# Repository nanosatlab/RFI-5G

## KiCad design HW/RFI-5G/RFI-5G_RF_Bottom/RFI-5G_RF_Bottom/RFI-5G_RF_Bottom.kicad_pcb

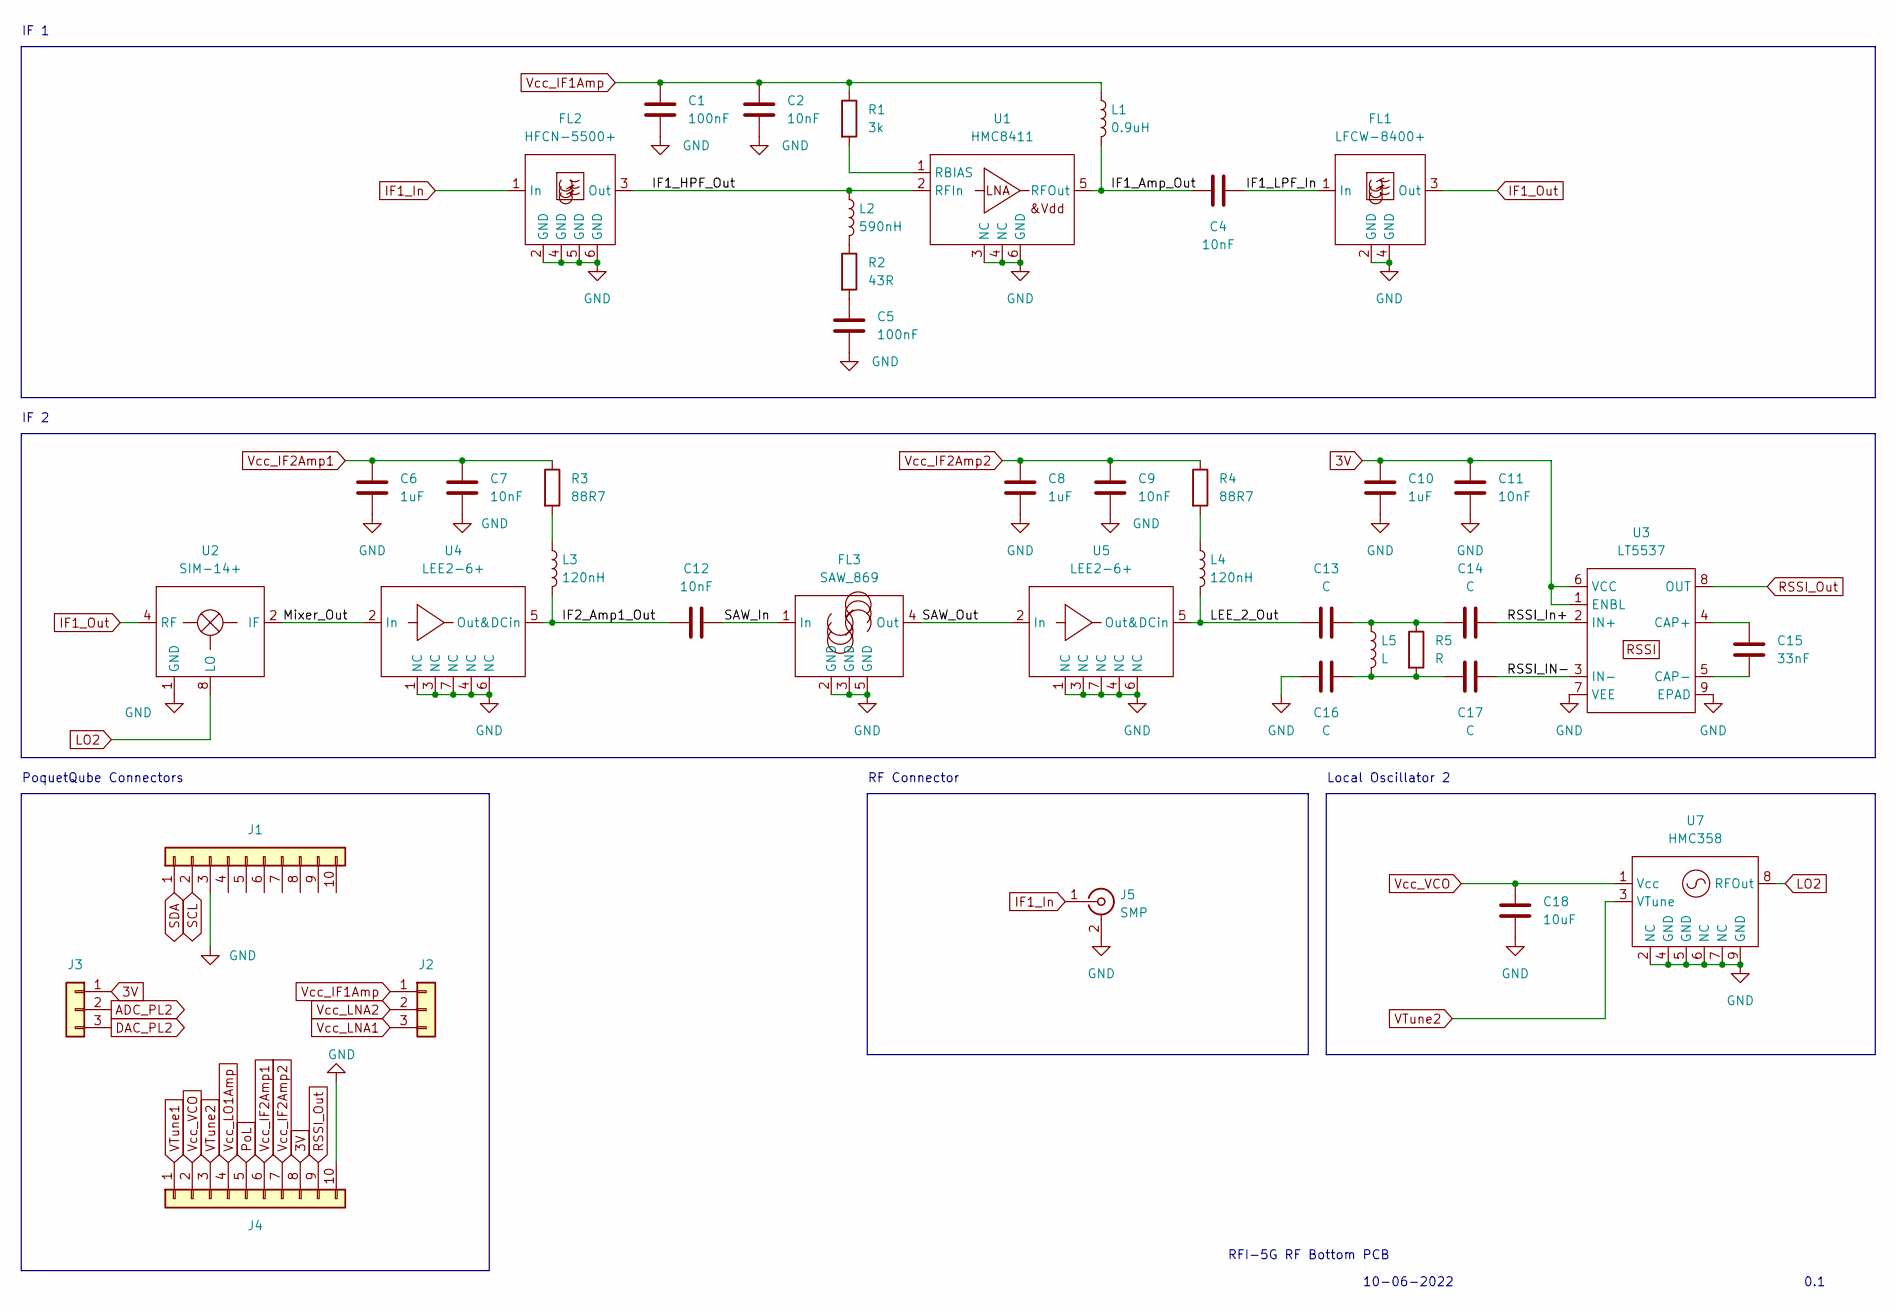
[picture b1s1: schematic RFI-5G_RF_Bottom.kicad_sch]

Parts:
C1, C5: 100nF; C_0402_1005Metric
C2, C4, C7, C9, C11, C12: 10nF; C_0402_1005Metric
C6, C8, C10: 1uF; C_0402_1005Metric
C13, C14, C16, C17: C; C_0402_1005Metric
C15: 33nF; C_0402_1005Metric
C18: 10uF; C_0402_1005Metric
FL1: LFCW-8400+; JC0603C-1
FL2: HFCN-5500+; JC0603C
FL3: SAW_869; QCS5P
J1, J4: Conn_01x10; PinHeader_1x10_P2.54mm_Vertical
J2, J3: Conn_01x03; PinHeader_1x03_P2.54mm_Vertical
J5: SMP; SMP_StraightPlugPCB
L1: 0.9uH; L_0603_1608Metric
L2: 590nH; L_0603_1608Metric
L3, L4: 120nH; L_0603_1608Metric
L5: L; L_0603_1608Metric
R1: 3k; R_0603_1608Metric
R2: 43R; R_0603_1608Metric
R3, R4: 88R7; R_0603_1608Metric
R5: R; R_0603_1608Metric
U1: HMC8411; 6-LFCSP
U2: SIM-14+; HV1195
U3: LT5537; DFN-8-1EP_2x3mm_P0.5mm_EP0.56x2.15mm
U4, U5: LEE2-6+; WSON-6-1EP_2x2mm_P0.65mm_EP1x1.6mm
U7: HMC358; MSOP-8-1EP_3x3mm_P0.65mm_EP2.5x3mm_Mask1.73x2.36mm

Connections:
3V: C10.2, C11.2, J3.1, J4.8, U3.1 (ENBL), U3.6 (VCC)
/IF1_Amp_Out: C4.1, L1.2, U1.5 (RFOut)
/IF1_HPF_Out: FL2.3 (Out), L2.1, U1.2 (RFIn)
/IF1_LPF_In: C4.2, FL1.1 (In)
/IF2_Amp1_Out: C12.1, L3.2, U4.5 (Out&DCin)
/LEE_2_Out: C13.1, L4.2, U5.5 (Out&DCin)
/Mixer_Out: U2.2 (IF), U4.2 (In)
/RSSI_IN-: C17.2, U3.3 (IN-)
/RSSI_In+: C14.2, U3.2 (IN+)
/SAW_In: C12.2, FL3.1 (In)
/SAW_Out: FL3.4 (Out), U5.2 (In)
ADC_PL2: J3.2
DAC_PL2: J3.3
GND: C1.1, C2.1, C5.1, C6.1, C7.1, C8.1, C9.1, C10.1, C11.1, C16.1, C18.1, FL1.2 (GND), FL1.4 (GND), FL2.2 (GND), FL2.4 (GND), FL2.5 (GND), FL2.6 (GND), FL3.2 (GND), FL3.3 (GND), FL3.5 (GND), J1.3, J4.10, J5.2 (Ext), U1.3 (NC), U1.4 (NC), U1.6 (GND), U2.1 (GND), U3.7 (VEE), U3.9 (EPAD), U4.1 (NC), U4.3 (NC), U4.4 (NC), U4.6 (NC), U4.7 (NC), U5.1 (NC), U5.3 (NC), U5.4 (NC), U5.6 (NC), U5.7 (NC), U7.2 (NC), U7.4 (GND), U7.5 (GND), U7.6 (NC), U7.7 (NC), U7.9 (GND)
IF1_In: FL2.1 (In), J5.1 (In)
IF1_Out: FL1.3 (Out), U2.4 (RF)
LO2: U2.8 (LO), U7.8 (RFOut)
unnamed: C5.2, R2.2
unnamed: C13.2, C14.1, L5.1, R5.1
unnamed: C15.1, U3.4 (CAP+)
unnamed: C15.2, U3.5 (CAP-)
unnamed: C16.2, C17.1, L5.2, R5.2
unnamed: L2.2, R2.1
unnamed: L3.1, R3.2
unnamed: L4.1, R4.2
unnamed: R1.2, U1.1 (RBIAS)
PoL: J4.5
RSSI_Out: J4.9, U3.8 (OUT)
SCL: J1.2
SDA: J1.1
VTune1: J4.1
VTune2: J4.3, U7.3 (VTune)
Vcc_IF1Amp: C1.2, C2.2, J2.1, L1.1, R1.1
Vcc_IF2Amp1: C6.2, C7.2, J4.6, R3.1
Vcc_IF2Amp2: C8.2, C9.2, J4.7, R4.1
Vcc_LNA1: J2.3
Vcc_LNA2: J2.2
Vcc_LO1Amp: J4.4
Vcc_VCO: C18.2, J4.2, U7.1 (Vcc)

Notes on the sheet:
Local Oscillator 2
0.1
IF 2
IF 1
RFI-5G RF Bottom PCB
RF Connector
10-06-2022
PoquetQube Connectors

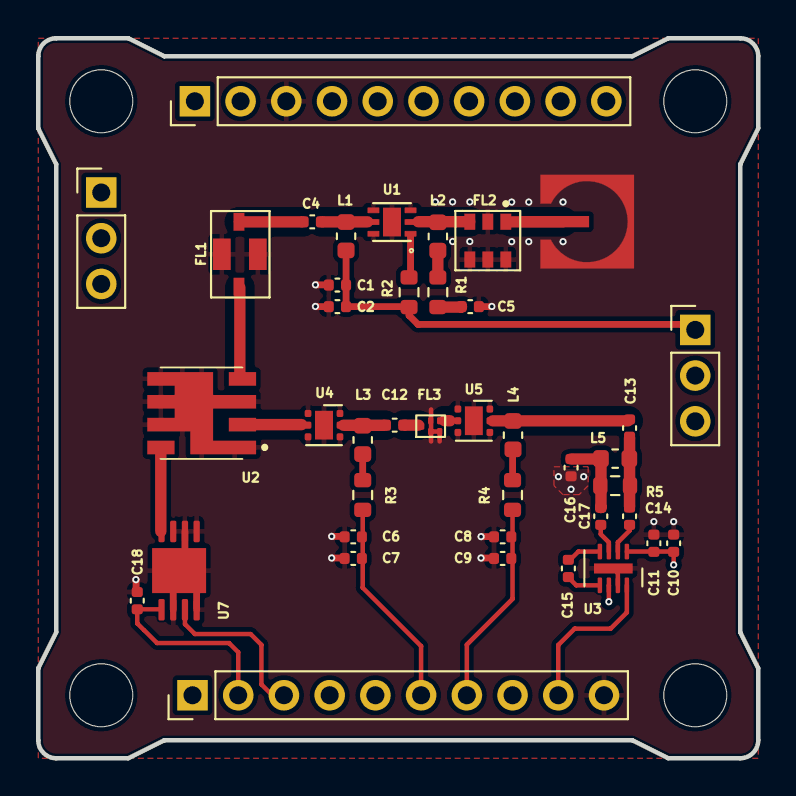
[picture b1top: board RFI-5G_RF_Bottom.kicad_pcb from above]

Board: 2 copper layers, 40.0 x 40.0 mm, 41 parts (0 on the bottom side), 30 nets.

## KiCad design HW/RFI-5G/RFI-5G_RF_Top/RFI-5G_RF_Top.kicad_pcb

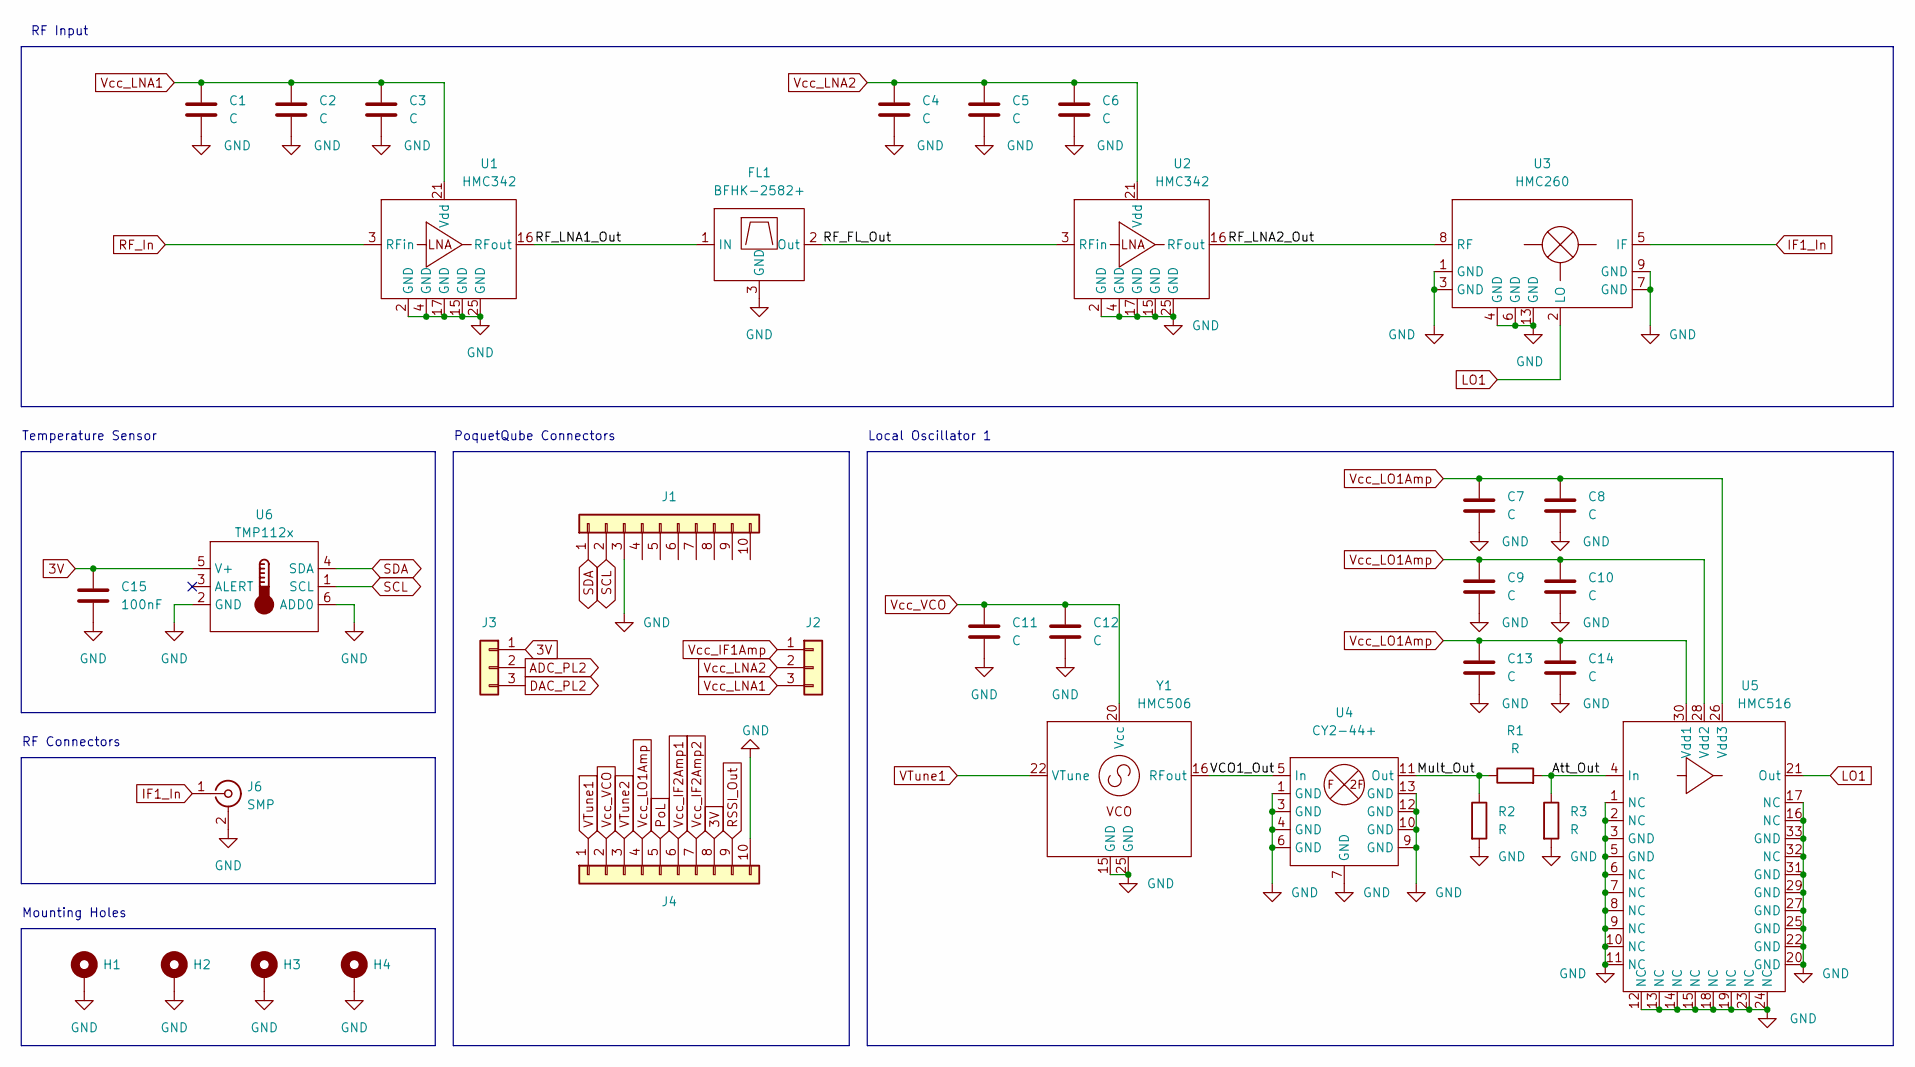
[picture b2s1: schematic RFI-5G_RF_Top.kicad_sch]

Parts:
C1, C2, C3, C4, C5, C6, C7, C8, C9, C10, C11, C12, C13, C14: C; C_0402_1005Metric
C15: 100nF; C_0402_1005Metric
FL1: BFHK-2582+; NM1812C-2
H1, H2, H3, H4: MountingHole_Pad
J1, J4: Conn_01x10; PinHeader_1x10_P2.54mm_Vertical
J2, J3: Conn_01x03; PinHeader_1x03_P2.54mm_Vertical
J6: SMP; SMP_StraightPlugPCB
R1, R2, R3: R; R_0402_1005Metric
U1, U2: HMC342; QFN-24-1EP_4x4mm_P0.5mm_EP2.6x2.6mm
U3: HMC260; QFN-12-1EP_3x3mm_P0.5mm_EP1.6x1.6mm
U4: CY2-44+; QFN-12-1EP_3x3mm_P0.5mm_EP1.65x1.65mm
U5: HMC516; QFN-32-1EP_5x5mm_P0.5mm_EP3.6x3.6mm
U6: TMP112x; SOT-563
Y1: HMC506; QFN-24-1EP_4x4mm_P0.5mm_EP2.7x2.7mm

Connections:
3V: C15.2, J3.1, J4.8, U6.5 (V+)
/Att_Out: R1.2, R3.1, U5.4 (In)
/Mult_Out: R1.1, R2.1, U4.11 (Out)
/RF_FL_Out: FL1.2 (Out), U2.3 (RFin)
/RF_LNA1_Out: FL1.1 (IN), U1.16 (RFout)
/RF_LNA2_Out: U2.16 (RFout), U3.8 (RF)
/VCO1_Out: U4.5 (In), Y1.16 (RFout)
ADC_PL2: J3.2
DAC_PL2: J3.3
GND: C1.2, C2.2, C3.2, C4.2, C5.2, C6.2, C7.2, C8.2, C9.2, C10.2, C11.2, C12.2, C13.2, C14.2, C15.1, FL1.3 (GND), H1.1, H2.1, H3.1, H4.1, J1.3, J4.10, J6.2 (Ext), R2.2, R3.2, U1.2 (GND), U1.4 (GND), U1.15 (GND), U1.17 (GND), U1.25 (GND), U2.2 (GND), U2.4 (GND), U2.15 (GND), U2.17 (GND), U2.25 (GND), U3.1 (GND), U3.3 (GND), U3.4 (GND), U3.6 (GND), U3.7 (GND), U3.9 (GND), U3.13 (GND), U4.1 (GND), U4.3 (GND), U4.4 (GND), U4.6 (GND), U4.7 (GND), U4.9 (GND), U4.10 (GND), U4.12 (GND), U4.13 (GND), U5.1 (NC), U5.2 (NC), U5.3 (GND), U5.5 (GND), U5.6 (NC), U5.7 (NC), U5.8 (NC), U5.9 (NC), U5.10 (NC), U5.11 (NC), U5.12 (NC), U5.13 (NC), U5.14 (NC), U5.15 (NC), U5.16 (NC), U5.17 (NC), U5.18 (NC), U5.19 (NC), U5.20 (GND), U5.22 (GND), U5.23 (NC), U5.24 (NC), U5.25 (GND), U5.27 (GND), U5.29 (GND), U5.31 (GND), U5.32 (NC), U5.33 (GND), U6.2 (GND), U6.6 (ADD0), Y1.15 (GND), Y1.25 (GND)
IF1_In: J6.1 (In), U3.5 (IF)
LO1: U3.2 (LO), U5.21 (Out)
PoL: J4.5
RF_In: U1.3 (RFin)
RSSI_Out: J4.9
SCL: J1.2, U6.1 (SCL)
SDA: J1.1, U6.4 (SDA)
VTune1: J4.1, Y1.22 (VTune)
VTune2: J4.3
Vcc_IF1Amp: J2.1
Vcc_IF2Amp1: J4.6
Vcc_IF2Amp2: J4.7
Vcc_LNA1: C1.1, C2.1, C3.1, J2.3, U1.21 (Vdd)
Vcc_LNA2: C4.1, C5.1, C6.1, J2.2, U2.21 (Vdd)
Vcc_LO1Amp: C7.1, C8.1, C9.1, C10.1, C13.1, C14.1, J4.4, U5.26 (Vdd3), U5.28 (Vdd2), U5.30 (Vdd1)
Vcc_VCO: C11.1, C12.1, J4.2, Y1.20 (Vcc)

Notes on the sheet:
Mounting Holes
PoquetQube Connectors
RF Input
Temperature Sensor
RF Connectors
Local Oscillator 1

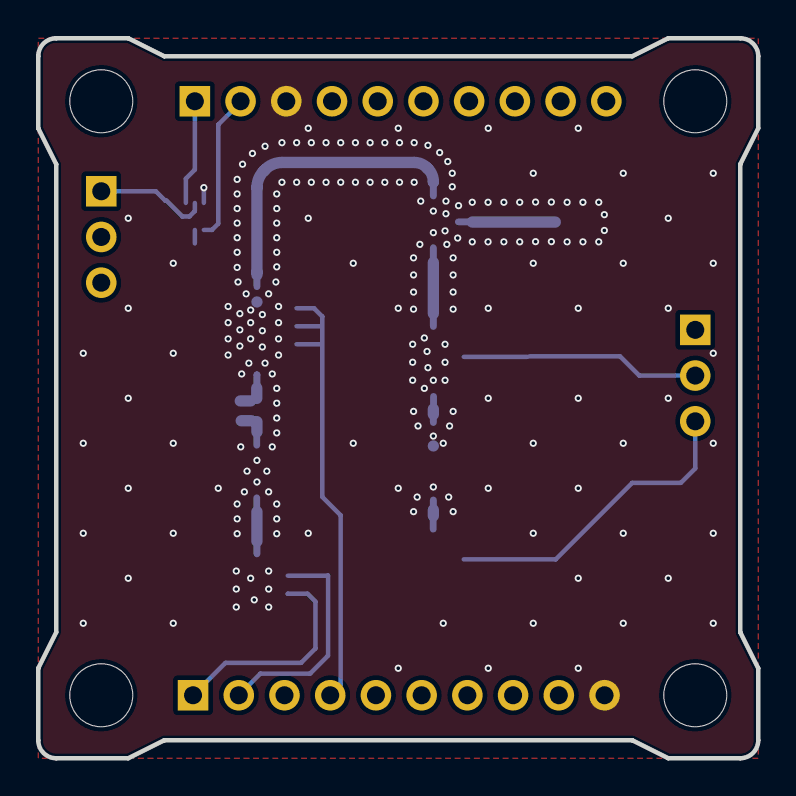
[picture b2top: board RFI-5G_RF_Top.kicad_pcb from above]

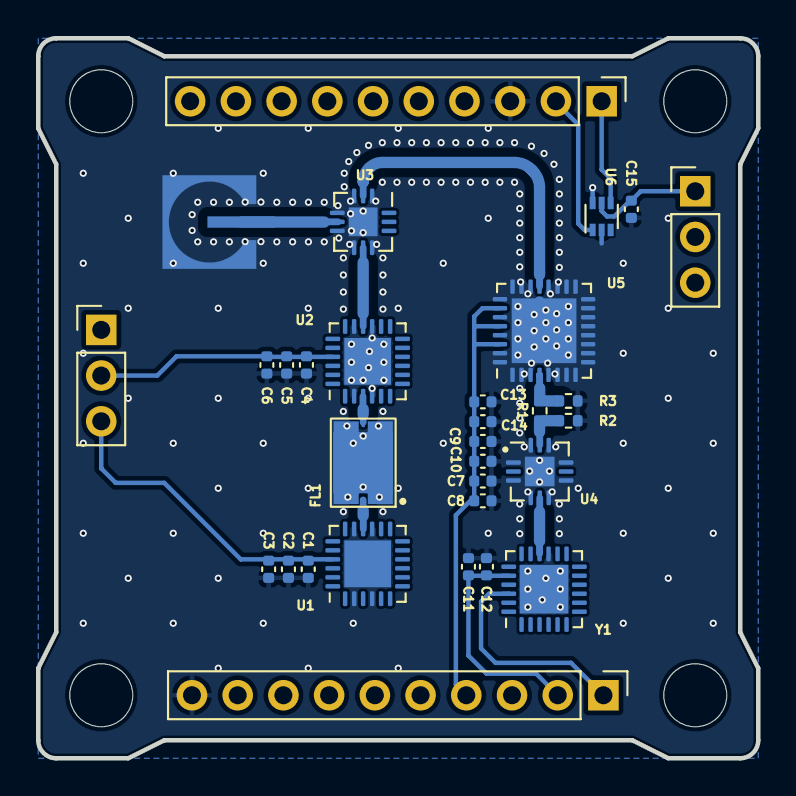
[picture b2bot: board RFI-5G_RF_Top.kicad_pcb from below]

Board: 2 copper layers, 40.0 x 40.0 mm, 35 parts (31 on the bottom side), 17 nets.

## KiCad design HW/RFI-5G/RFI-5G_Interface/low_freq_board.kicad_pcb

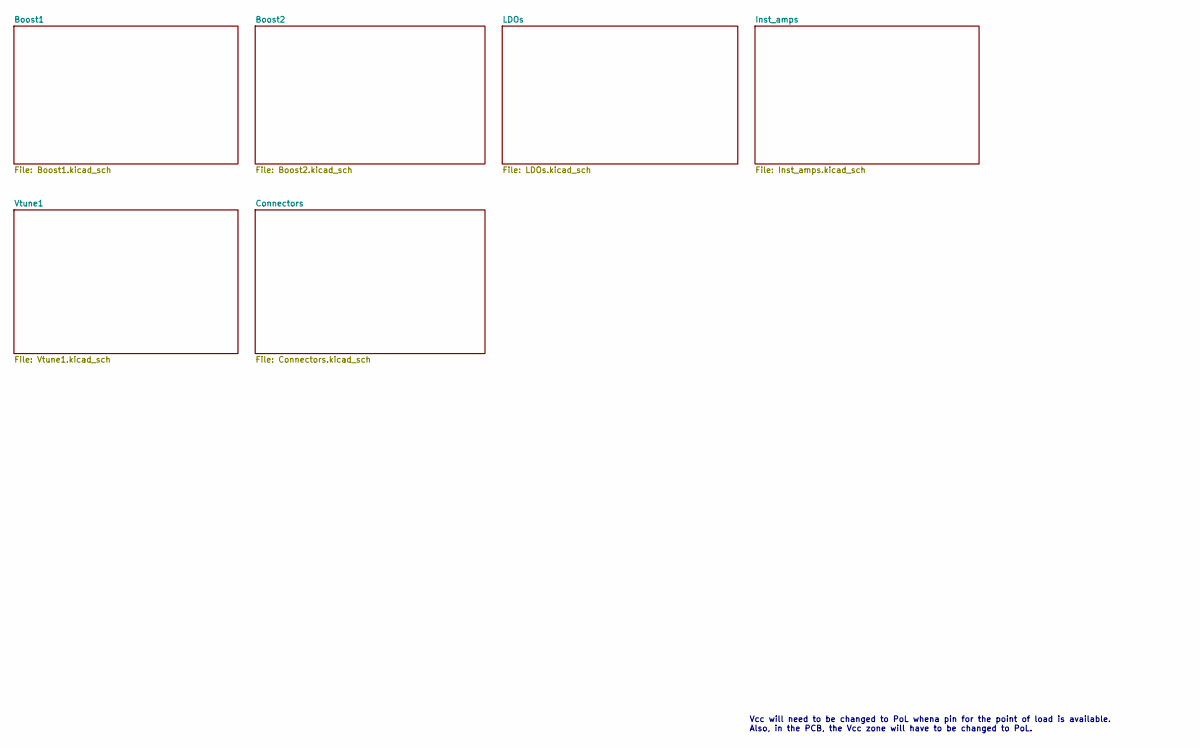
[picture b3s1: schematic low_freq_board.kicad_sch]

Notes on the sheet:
Vcc will need to be changed to PoL whena pin for the point of load is available. Also, in the PCB, the Vcc zone will have to be changed to PoL.

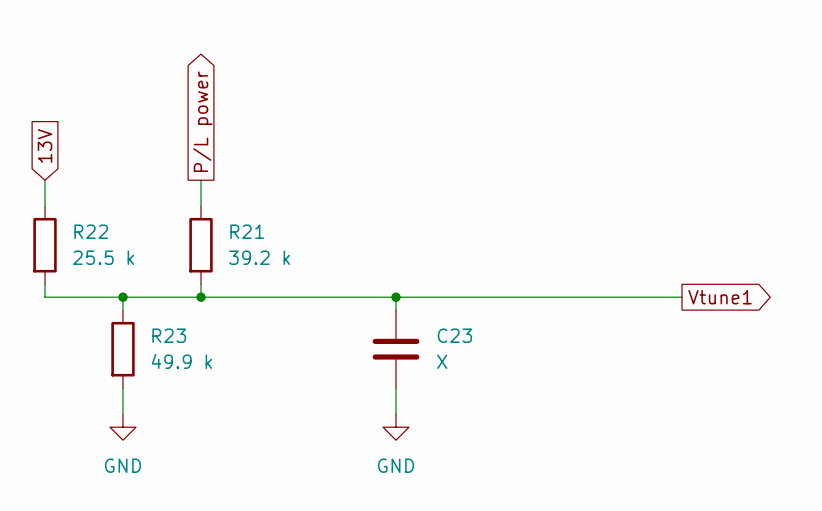
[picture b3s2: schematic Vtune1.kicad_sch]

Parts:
C23: X; C_0603_1608Metric_Pad1.08x0.95mm_HandSolder
R21: 39.2 k; R_0603_1608Metric_Pad0.98x0.95mm_HandSolder
R22: 25.5 k; R_0402_1005Metric_Pad0.72x0.64mm_HandSolder
R23: 49.9 k; R_0402_1005Metric_Pad0.72x0.64mm_HandSolder

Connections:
13V: R22.1; also elsewhere on the board
GND: C23.2, R23.2; also elsewhere on the board
P/L power: R21.1; also elsewhere on the board
Vtune1: C23.1, R21.2, R22.2, R23.1

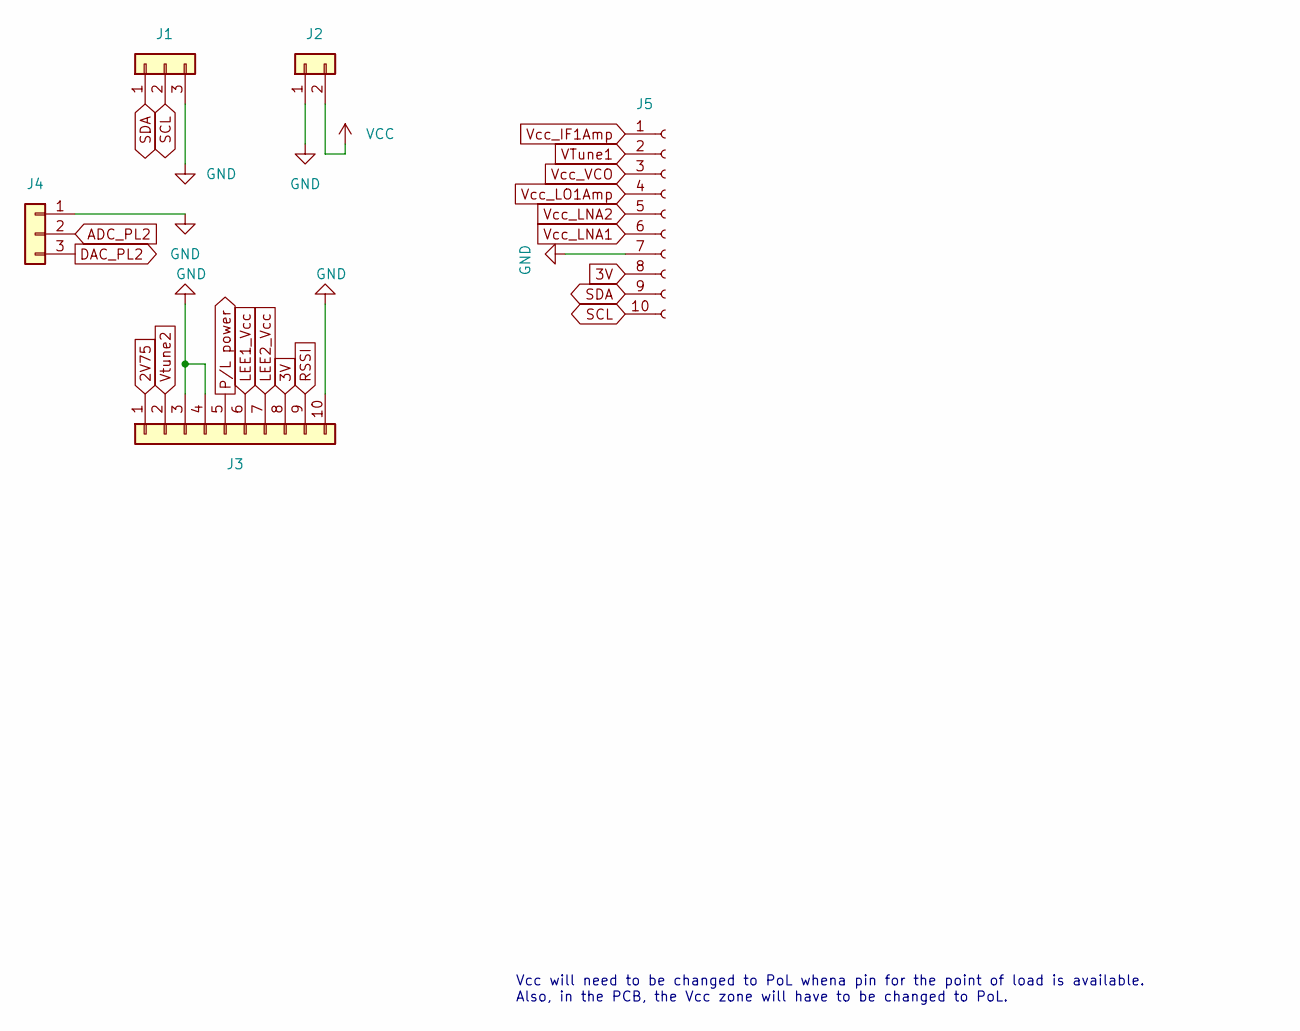
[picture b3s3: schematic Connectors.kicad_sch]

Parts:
J1, J4: Conn_01x03; PinHeader_1x03_P2.54mm_Vertical
J2: Conn_01x02; PinHeader_1x02_P2.54mm_Vertical
J3: Conn_01x10; PinHeader_1x10_P2.54mm_Vertical
J5: Conn_01x10_Female; PinHeader_1x10_P1.00mm_Vertical

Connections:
2V75: J3.1; also elsewhere on the board
3V: J3.8, J5.8; also elsewhere on the board
ADC_PL2: J4.2; also elsewhere on the board
DAC_PL2: J4.3; also elsewhere on the board
GND: J1.3, J2.1, J3.3, J3.4, J3.10, J4.1, J5.7; also elsewhere on the board
LEE1_Vcc: J3.6; also elsewhere on the board
LEE2_Vcc: J3.7; also elsewhere on the board
P/L power: J3.5; also elsewhere on the board
RSSI: J3.9; also elsewhere on the board
SCL: J1.2, J5.10
SDA: J1.1, J5.9
VCC: J2.2
VTune1: J5.2
Vcc_IF1Amp: J5.1
Vcc_LNA1: J5.6
Vcc_LNA2: J5.5
Vcc_LO1Amp: J5.4
Vcc_VCO: J5.3
Vtune2: J3.2; also elsewhere on the board

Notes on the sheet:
Vcc will need to be changed to PoL whena pin for the point of load is available. Also, in the PCB, the Vcc zone will have to be changed to PoL.

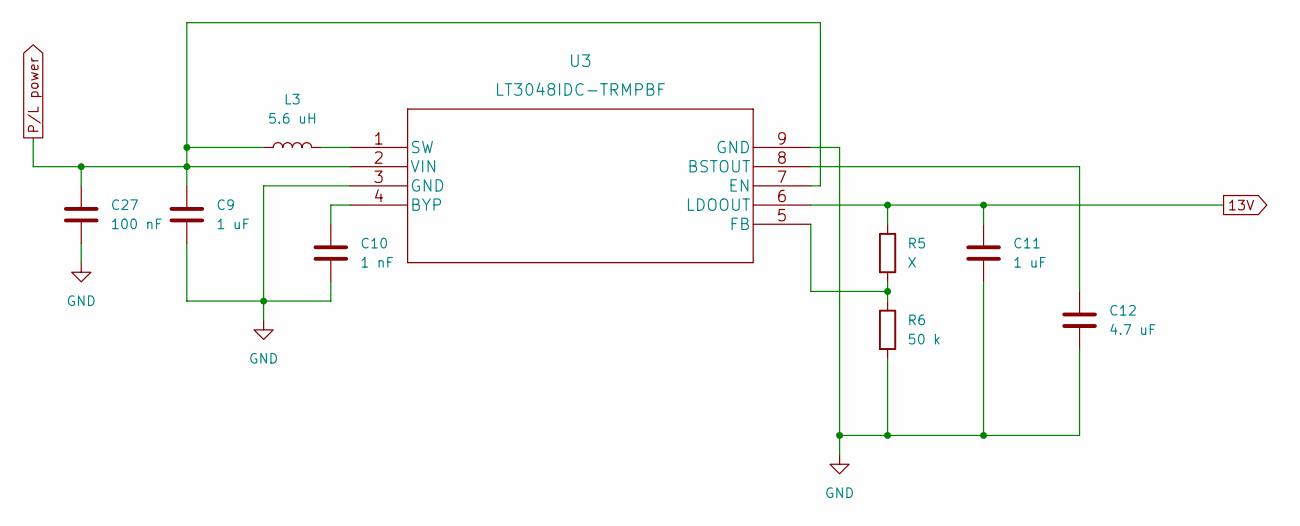
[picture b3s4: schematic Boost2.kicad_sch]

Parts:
C9, C11: 1 uF; C_0603_1608Metric_Pad1.08x0.95mm_HandSolder
C10: 1 nF; C_0603_1608Metric_Pad1.08x0.95mm_HandSolder
C12: 4.7 uF; C_0603_1608Metric_Pad1.08x0.95mm_HandSolder
C27: 100 nF; C_0603_1608Metric_Pad1.08x0.95mm_HandSolder
L3: 5.6 uH; ASPI-4030S-100M-T
R5: X; R_0603_1608Metric_Pad0.98x0.95mm_HandSolder
R6: 50 k; R_0603_1608Metric_Pad0.98x0.95mm_HandSolder
U3: LT3048IDC-TRMPBF

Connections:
13V: C11.1, R5.1, U3.6 (LDOOUT); also elsewhere on the board
GND: C9.2, C10.2, C11.2, C12.2, C27.2, R6.2, U3.3 (GND), U3.9 (GND); also elsewhere on the board
unnamed: C10.1, U3.4 (BYP)
unnamed: C12.1, U3.8 (BSTOUT)
unnamed: L3.2, U3.1 (SW)
unnamed: R5.2, R6.1, U3.5 (FB)
P/L power: C9.1, C27.1, L3.1, U3.2 (VIN), U3.7 (EN); also elsewhere on the board

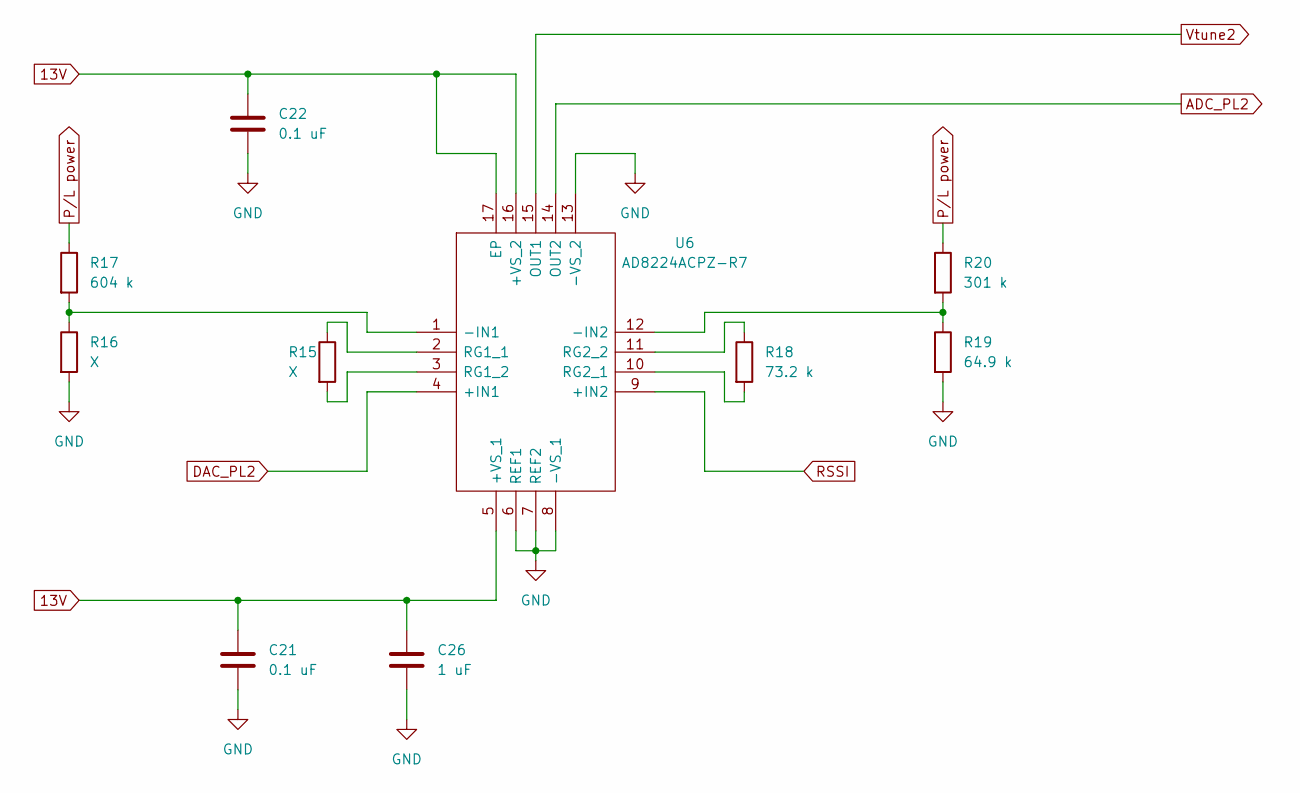
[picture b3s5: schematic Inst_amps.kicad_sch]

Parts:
C21, C22: 0.1 uF; C_0402_1005Metric_Pad0.74x0.62mm_HandSolder
C26: 1 uF; C_0603_1608Metric_Pad1.08x0.95mm_HandSolder
R15, R16: X; R_0603_1608Metric_Pad0.98x0.95mm_HandSolder
R17: 604 k; R_0603_1608Metric_Pad0.98x0.95mm_HandSolder
R18: 73.2 k; R_0603_1608Metric_Pad0.98x0.95mm_HandSolder
R19: 64.9 k; R_0603_1608Metric_Pad0.98x0.95mm_HandSolder
R20: 301 k; R_0603_1608Metric_Pad0.98x0.95mm_HandSolder
U6: AD8224ACPZ-R7; QFN65P400X400X90-17N; Mouser Part Number 584-AD8224ACPZ-R7

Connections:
13V: C21.1, C22.1, C26.1, U6.5 (+VS_1), U6.16 (+VS_2), U6.17 (EP); also elsewhere on the board
ADC_PL2: U6.14 (OUT2); also elsewhere on the board
DAC_PL2: U6.4 (+IN1); also elsewhere on the board
GND: C21.2, C22.2, C26.2, R16.2, R19.2, U6.6 (REF1), U6.7 (REF2), U6.8 (-VS_1), U6.13 (-VS_2); also elsewhere on the board
unnamed: R15.1, U6.2 (RG1_1)
unnamed: R15.2, U6.3 (RG1_2)
unnamed: R16.1, R17.2, U6.1 (-IN1)
unnamed: R18.1, U6.11 (RG2_2)
unnamed: R18.2, U6.10 (RG2_1)
unnamed: R19.1, R20.2, U6.12 (-IN2)
P/L power: R17.1, R20.1; also elsewhere on the board
RSSI: U6.9 (+IN2); also elsewhere on the board
Vtune2: U6.15 (OUT1); also elsewhere on the board

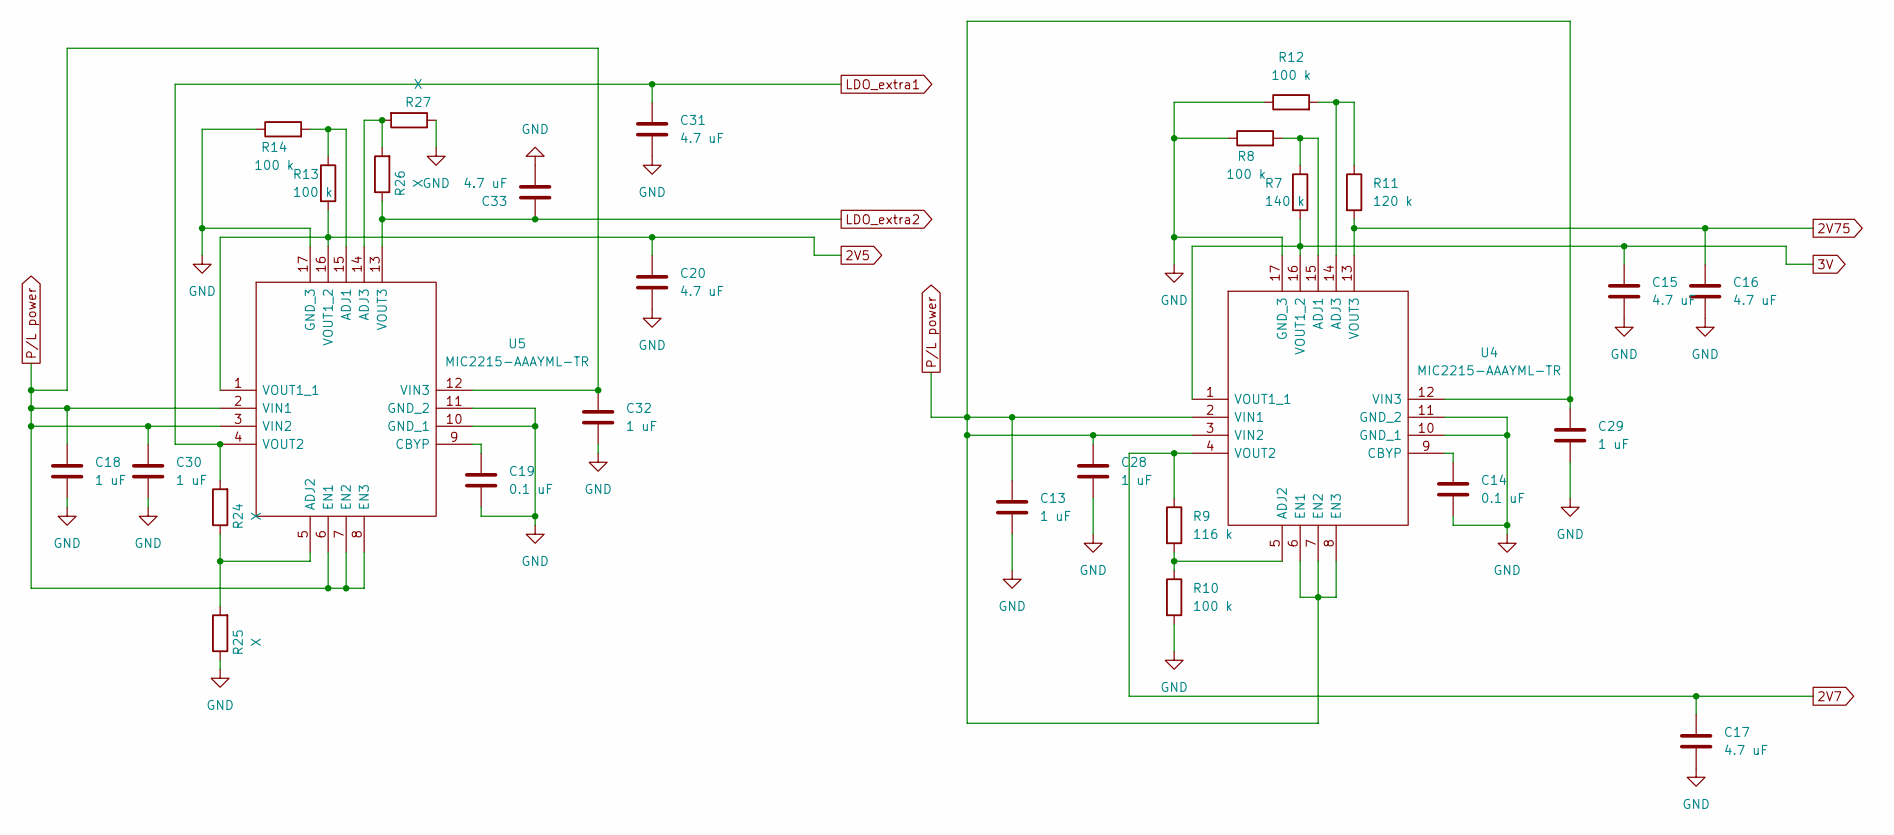
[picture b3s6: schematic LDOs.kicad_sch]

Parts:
C13, C18, C28, C29, C30, C32: 1 uF; C_0603_1608Metric_Pad1.08x0.95mm_HandSolder
C14, C19: 0.1 uF; C_0402_1005Metric_Pad0.74x0.62mm_HandSolder
C15, C16, C17, C20, C31, C33: 4.7 uF; C_0603_1608Metric_Pad1.08x0.95mm_HandSolder
R7: 140 k; R_0603_1608Metric_Pad0.98x0.95mm_HandSolder
R8, R10, R12, R13, R14: 100 k; R_0603_1608Metric_Pad0.98x0.95mm_HandSolder
R9: 116 k; R_0603_1608Metric_Pad0.98x0.95mm_HandSolder
R11: 120 k; R_0603_1608Metric_Pad0.98x0.95mm_HandSolder
R24, R25, R26, R27: X; R_0603_1608Metric_Pad0.98x0.95mm_HandSolder
U4, U5: MIC2215-AAAYML-TR; QFN65P400X400X90-17N; Mouser Part Number 998-MIC2215-AAAYMLTR

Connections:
2V5: C20.1, R13.2, U5.1 (VOUT1_1), U5.16 (VOUT1_2)
2V7: C17.1, R9.1, U4.4 (VOUT2)
2V75: C16.1, R11.2, U4.13 (VOUT3); also elsewhere on the board
3V: C15.1, R7.2, U4.1 (VOUT1_1), U4.16 (VOUT1_2); also elsewhere on the board
GND: C13.2, C14.2, C15.2, C16.2, C17.2, C18.2, C19.2, C20.2, C28.2, C29.2, C30.2, C31.2, C32.2, C33.2, R8.1, R10.2, R12.1, R14.1, R25.1, R27.1, U4.10 (GND_1), U4.11 (GND_2), U4.17 (GND_3), U5.10 (GND_1), U5.11 (GND_2), U5.17 (GND_3); also elsewhere on the board
LDO_extra1: C31.1, R24.2, U5.4 (VOUT2)
LDO_extra2: C33.1, R26.1, U5.13 (VOUT3)
unnamed: C14.1, U4.9 (CBYP)
unnamed: C19.1, U5.9 (CBYP)
unnamed: R7.1, R8.2, U4.15 (ADJ1)
unnamed: R9.2, R10.1, U4.5 (ADJ2)
unnamed: R11.1, R12.2, U4.14 (ADJ3)
unnamed: R13.1, R14.2, U5.15 (ADJ1)
unnamed: R24.1, R25.2, U5.5 (ADJ2)
unnamed: R26.2, R27.2, U5.14 (ADJ3)
P/L power: C13.1, C18.1, C28.1, C29.1, C30.1, C32.1, U4.2 (VIN1), U4.3 (VIN2), U4.6 (EN1), U4.7 (EN2), U4.8 (EN3), U4.12 (VIN3), U5.2 (VIN1), U5.3 (VIN2), U5.6 (EN1), U5.7 (EN2), U5.8 (EN3), U5.12 (VIN3); also elsewhere on the board

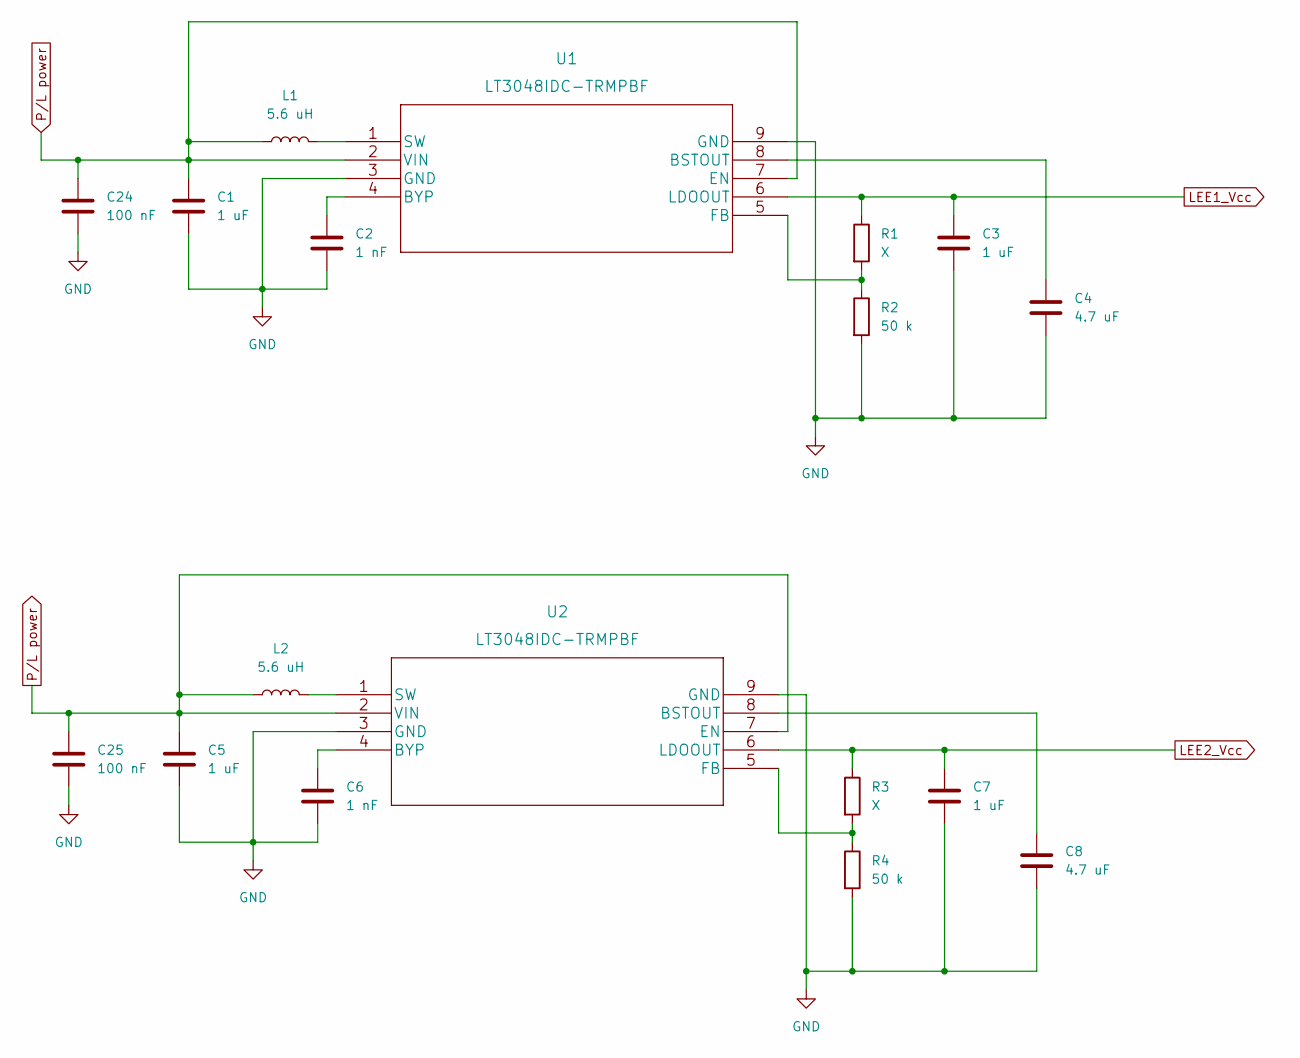
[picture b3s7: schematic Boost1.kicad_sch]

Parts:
C1, C3, C5, C7: 1 uF; C_0603_1608Metric_Pad1.08x0.95mm_HandSolder
C2, C6: 1 nF; C_0603_1608Metric_Pad1.08x0.95mm_HandSolder
C4, C8: 4.7 uF; C_0603_1608Metric_Pad1.08x0.95mm_HandSolder
C24, C25: 100 nF; C_0603_1608Metric_Pad1.08x0.95mm_HandSolder
L1, L2: 5.6 uH; ASPI-4030S-100M-T
R1, R3: X; R_0603_1608Metric_Pad0.98x0.95mm_HandSolder
R2, R4: 50 k; R_0603_1608Metric_Pad0.98x0.95mm_HandSolder
U1, U2: LT3048IDC-TRMPBF

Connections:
GND: C1.2, C2.2, C3.2, C4.2, C5.2, C6.2, C7.2, C8.2, C24.2, C25.2, R2.2, R4.2, U1.3 (GND), U1.9 (GND), U2.3 (GND), U2.9 (GND); also elsewhere on the board
LEE1_Vcc: C3.1, R1.1, U1.6 (LDOOUT); also elsewhere on the board
LEE2_Vcc: C7.1, R3.1, U2.6 (LDOOUT); also elsewhere on the board
unnamed: C2.1, U1.4 (BYP)
unnamed: C4.1, U1.8 (BSTOUT)
unnamed: C6.1, U2.4 (BYP)
unnamed: C8.1, U2.8 (BSTOUT)
unnamed: L1.2, U1.1 (SW)
unnamed: L2.2, U2.1 (SW)
unnamed: R1.2, R2.1, U1.5 (FB)
unnamed: R3.2, R4.1, U2.5 (FB)
P/L power: C1.1, C5.1, C24.1, C25.1, L1.1, L2.1, U1.2 (VIN), U1.7 (EN), U2.2 (VIN), U2.7 (EN); also elsewhere on the board

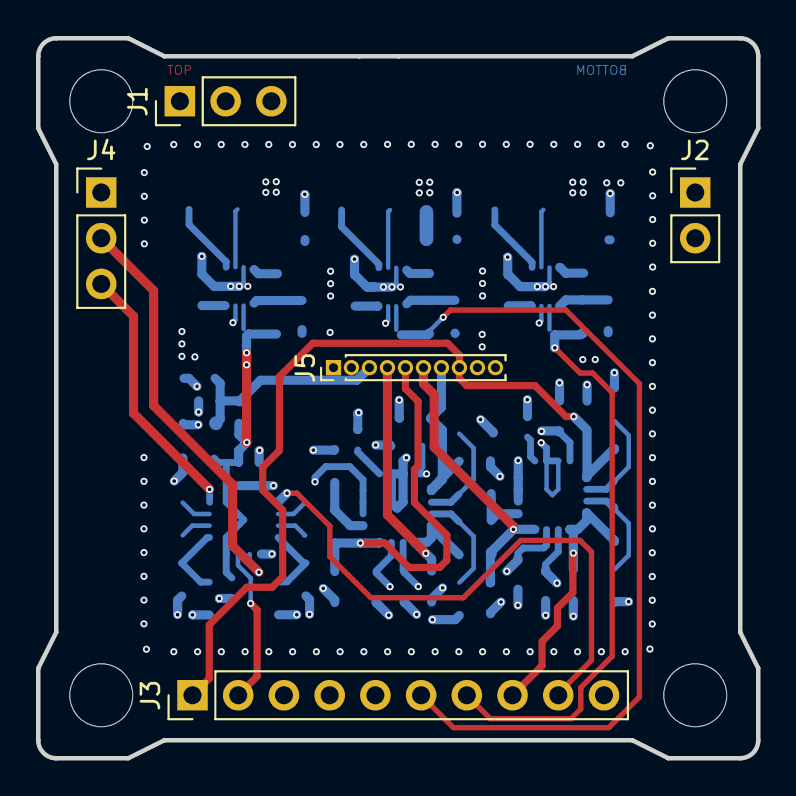
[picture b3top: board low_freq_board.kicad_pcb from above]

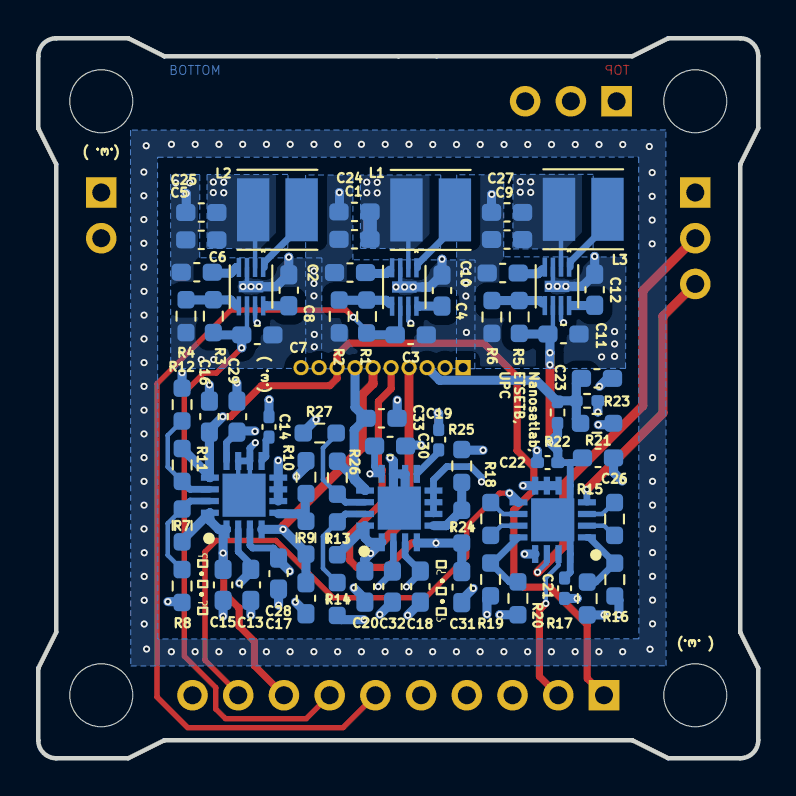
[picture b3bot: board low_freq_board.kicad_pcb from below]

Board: 4 copper layers, 40.0 x 40.0 mm, 74 parts (69 on the bottom side), 44 nets.

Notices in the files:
parts and their libraries:
Copyright 2021 Accelerated Designs. All rights reserved.
